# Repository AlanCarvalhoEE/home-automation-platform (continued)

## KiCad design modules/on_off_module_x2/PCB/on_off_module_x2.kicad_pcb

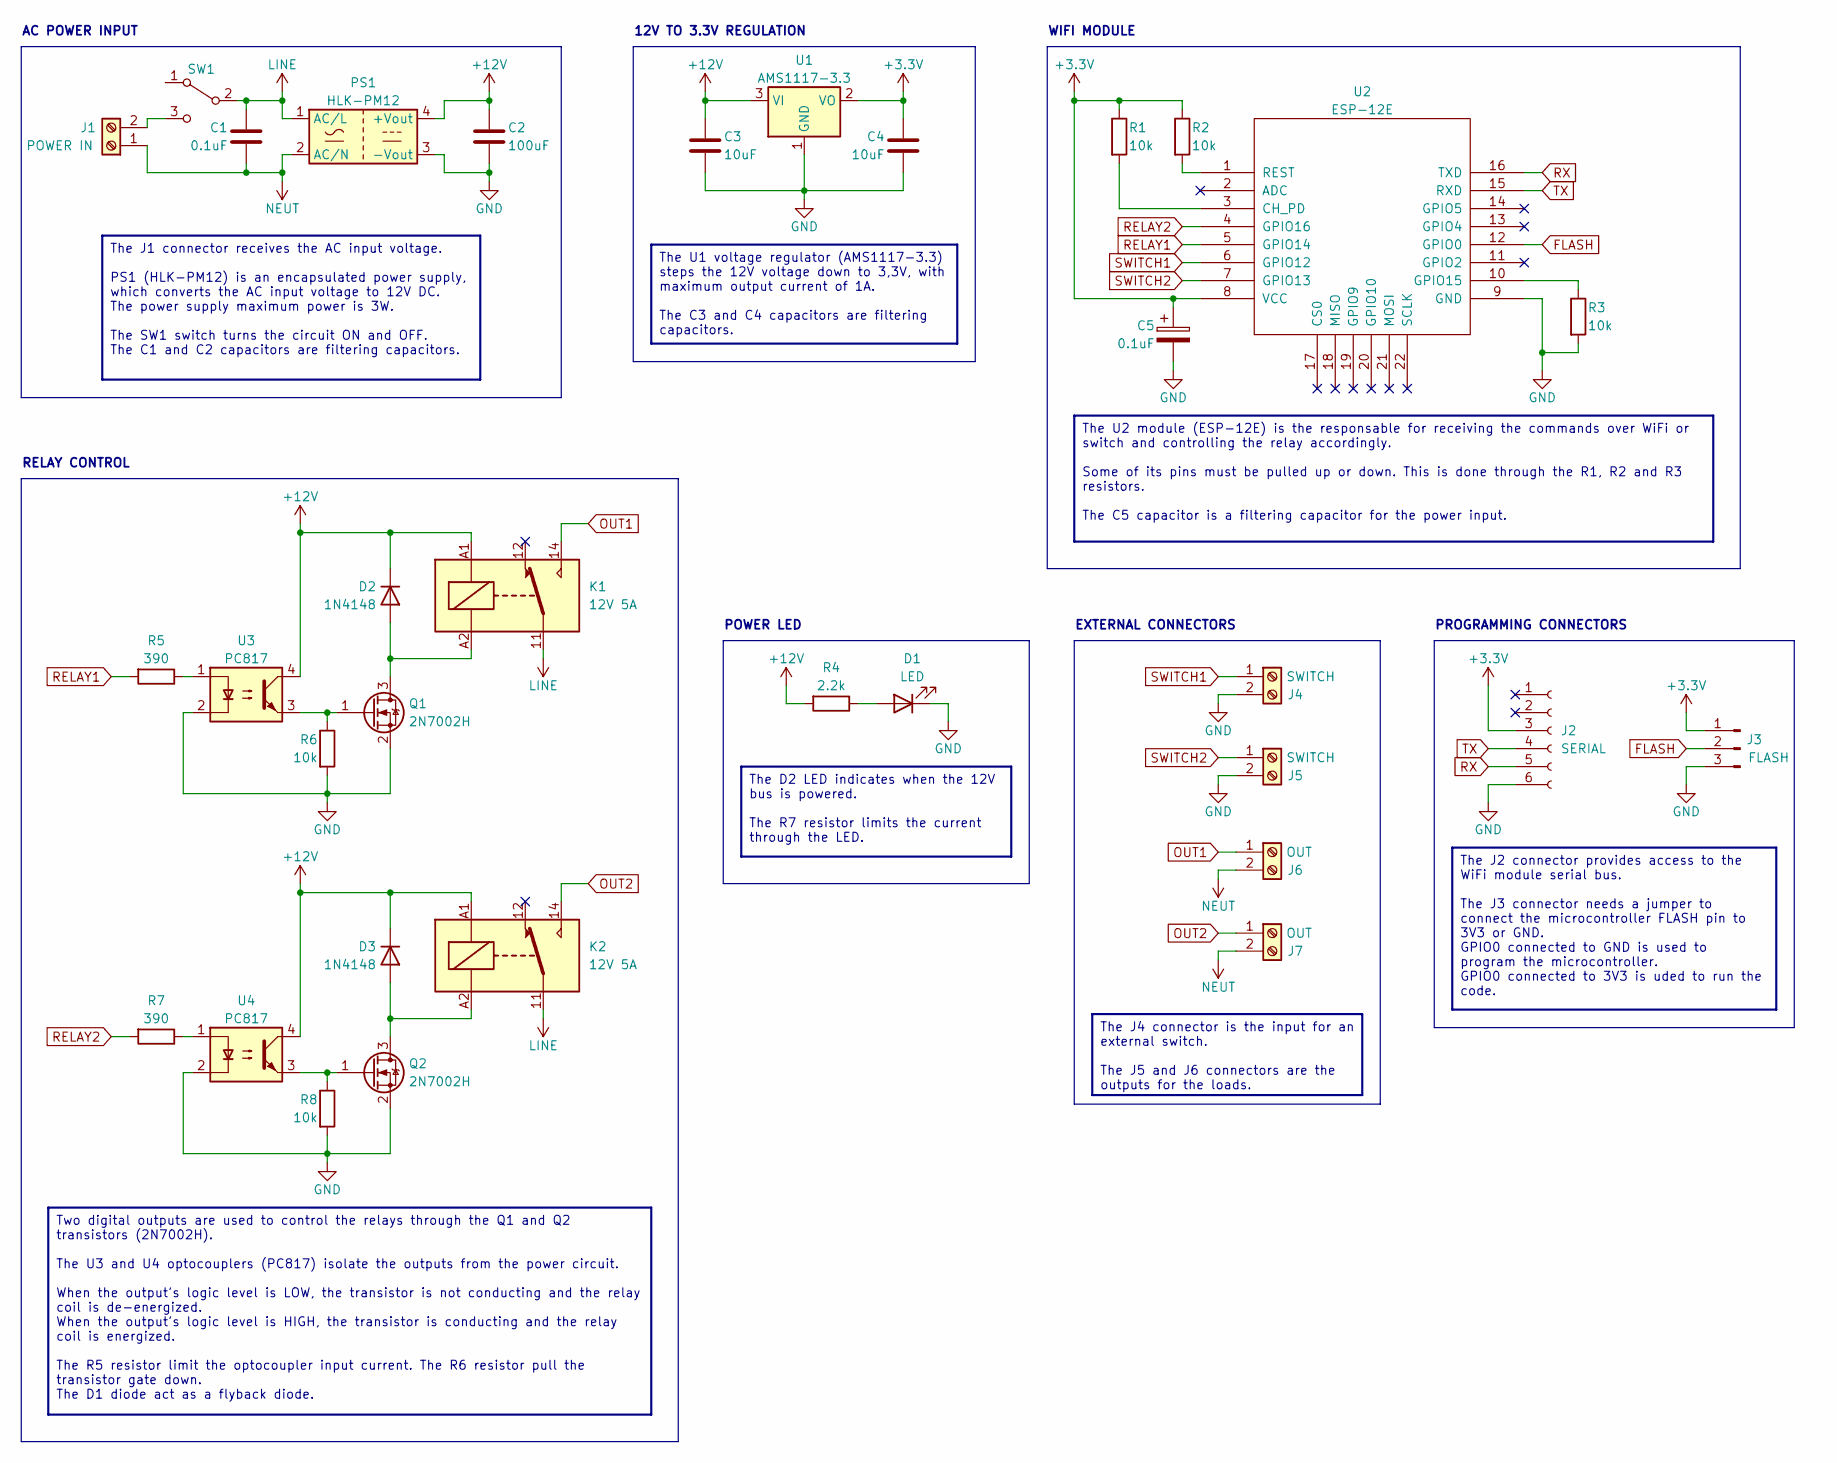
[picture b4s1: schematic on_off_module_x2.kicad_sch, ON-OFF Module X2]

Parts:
C1: 0.1uF; C_Rect_L18.0mm_W6.0mm_P15.00mm_FKS3_FKP3; Voltage 275V
C2: 100uF; CP_Elec_6.3x7.7; Voltage 16V
C3: 10uF; CP_EIA-3216-18_Kemet-A; Voltage 16V
C4: 10uF; CP_EIA-3216-18_Kemet-A; Voltage 6.3V
C5: 0.1uF; C_0603_1608Metric; Voltage 6.3V
D1: LED; LED_0603_1608Metric
D2, D3: 1N4148; D_SOD-323F
J1, J4, J5, J6, J7: Screw_Terminal_01x02; TerminalBlock_Phoenix_MKDS-1,5-2-5.08_1x02_P5.08mm_Horizont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
J2: Conn_01x06_Socket; PinHeader_1x06_P2.54mm_Vertical
J3: Conn_01x03_Socket; PinSocket_1x03_P2.54mm_Vertical
K1, K2: 12V 5A; Relay_SPDT_Finder_36.11
PS1: HLK-PM12; Converter_ACDC_HiLink_HLK-PMxx
Q1, Q2: 2N7002H; SOT-23
R1, R2, R3, R6, R8: 10k; R_0603_1608Metric; Tolerance 5%
R4: 2.2k; R_0603_1608Metric; Tolerance 5%
R5, R7: 390; R_0603_1608Metric; Tolerance 5%
SW1: SW_SPDT; Toggle_Switch_SelfLocking_7x7
U1: AMS1117-3.3; SOT-223-3_TabPin2
U2: ESP-12E; ESP-12E_SMD
U3, U4: PC817; SMDIP-4_W7.62mm

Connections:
+3.3V: C4.1, C5.1, J2.3, J3.1, R1.1, R2.1, U1.2 (VO), U2.8 (VCC)
+12V: C2.1, C3.1, D2.1 (K), D3.1 (K), K1.A1, K2.A1, PS1.4 (+Vout), R4.2, U1.3 (VI), U3.4, U4.4
FLASH: J3.2, U2.12 (GPIO0)
GND: C2.2, C3.2, C4.2, C5.2, D1.1 (K), J2.6, J3.3, J4.2, J5.2, PS1.3 (-Vout), Q1.2 (S), Q2.2 (S), R3.2, R6.2, R8.2, U1.1 (GND), U2.9 (GND), U3.2, U4.2
LINE: C1.1, K1.11, K2.11, PS1.1 (AC/L), SW1.2 (B)
NEUT: C1.2, J1.1, J6.2, J7.2, PS1.2 (AC/N)
unnamed: D1.2 (A), R4.1
unnamed: D2.2 (A), K1.A2, Q1.3 (D)
unnamed: D3.2 (A), K2.A2, Q2.3 (D)
unnamed: J1.2, SW1.3 (C)
unnamed: Q1.1 (G), R6.1, U3.3
unnamed: Q2.1 (G), R8.1, U4.3
unnamed: R5.1, U3.1
unnamed: R7.1, U4.1
unnamed: R1.2, U2.3 (CH_PD)
unnamed: R3.1, U2.10 (GPIO15)
unnamed: R2.2, U2.1 (REST)
OUT1: J6.1, K1.14
OUT2: J7.1, K2.14
RELAY1: R5.2, U2.5 (GPIO14)
RELAY2: R7.2, U2.4 (GPIO16)
RX: J2.5, U2.16 (TXD)
SWITCH1: J4.1, U2.6 (GPIO12)
SWITCH2: J5.1, U2.7 (GPIO13)
TX: J2.4, U2.15 (RXD)

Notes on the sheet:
The J1 connector receives the AC input voltage. PS1 (HLK-PM12) is an encapsulated power supply, which converts the AC input voltage to 12V DC. The power supply maximum power is 3W. The SW1 switch turns the circuit ON and OFF. The C1 and C2 capacitors are filtering capacitors.
Two digital outputs are used to control the relays through the Q1 and Q2 transistors (2N7002H). The U3 and U4 optocouplers (PC817) isolate the outputs from the power circuit. When the output's logic level is LOW, the transistor is not conducting and the relay coil is de-energized. When the output's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
The J2 connector provides access to the WiFi module serial bus. The J3 connector needs a jumper to connect the microcontroller FLASH pin to 3V3 or GND. GPIO0 connected to GND is used to program the microcontroller. GPIO0 connected to 3V3 is uded to run the code.
The D2 LED indicates when the 12V bus is powered. The R7 resistor limits the current through the LED.
The U2 module (ESP-12E) is the responsable for receiving the commands over WiFi or switch and controlling the relay accordingly. Some of its pins must be pulled up or down. This is done through the R1, R2 and R3 resistors. The C5 capacitor is a filtering capacitor for the power input.
The U1 voltage regulator (AMS1117-3.3) steps the 12V voltage down to 3,3V, with maximum output current of 1A. The C3 and C4 capacitors are filtering capacitors.
The J4 connector is the input for an external switch. The J5 and J6 connectors are the outputs for the loads.
PROGRAMMING CONNECTORS
RELAY CONTROL
POWER LED
AC POWER INPUT
EXTERNAL CONNECTORS
WIFI MODULE
12V TO 3.3V REGULATION

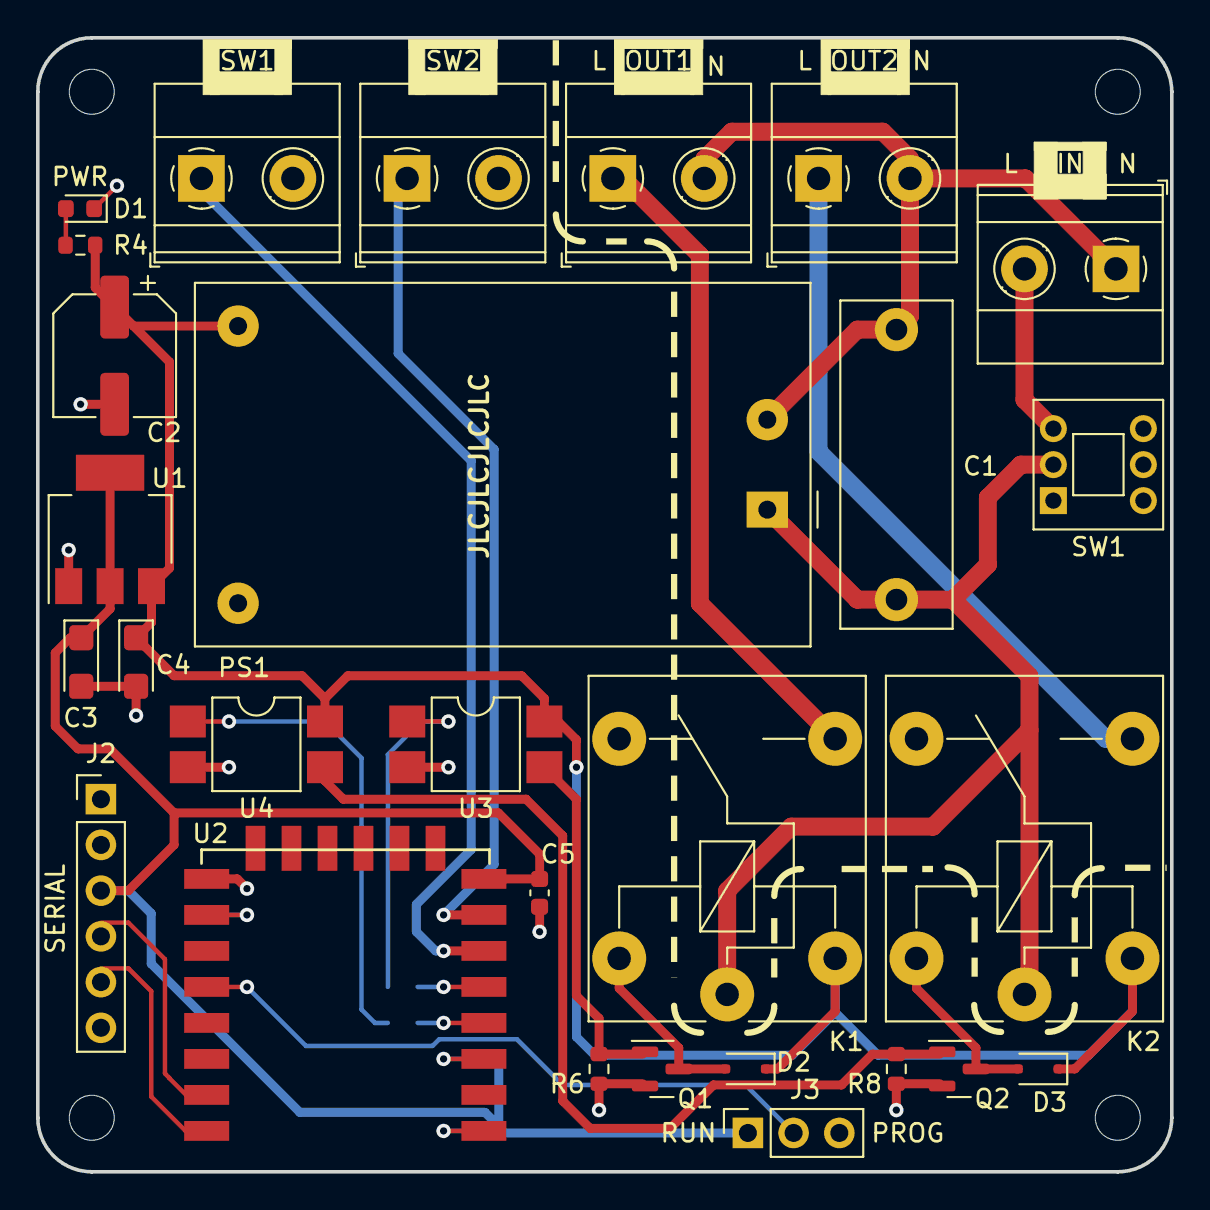
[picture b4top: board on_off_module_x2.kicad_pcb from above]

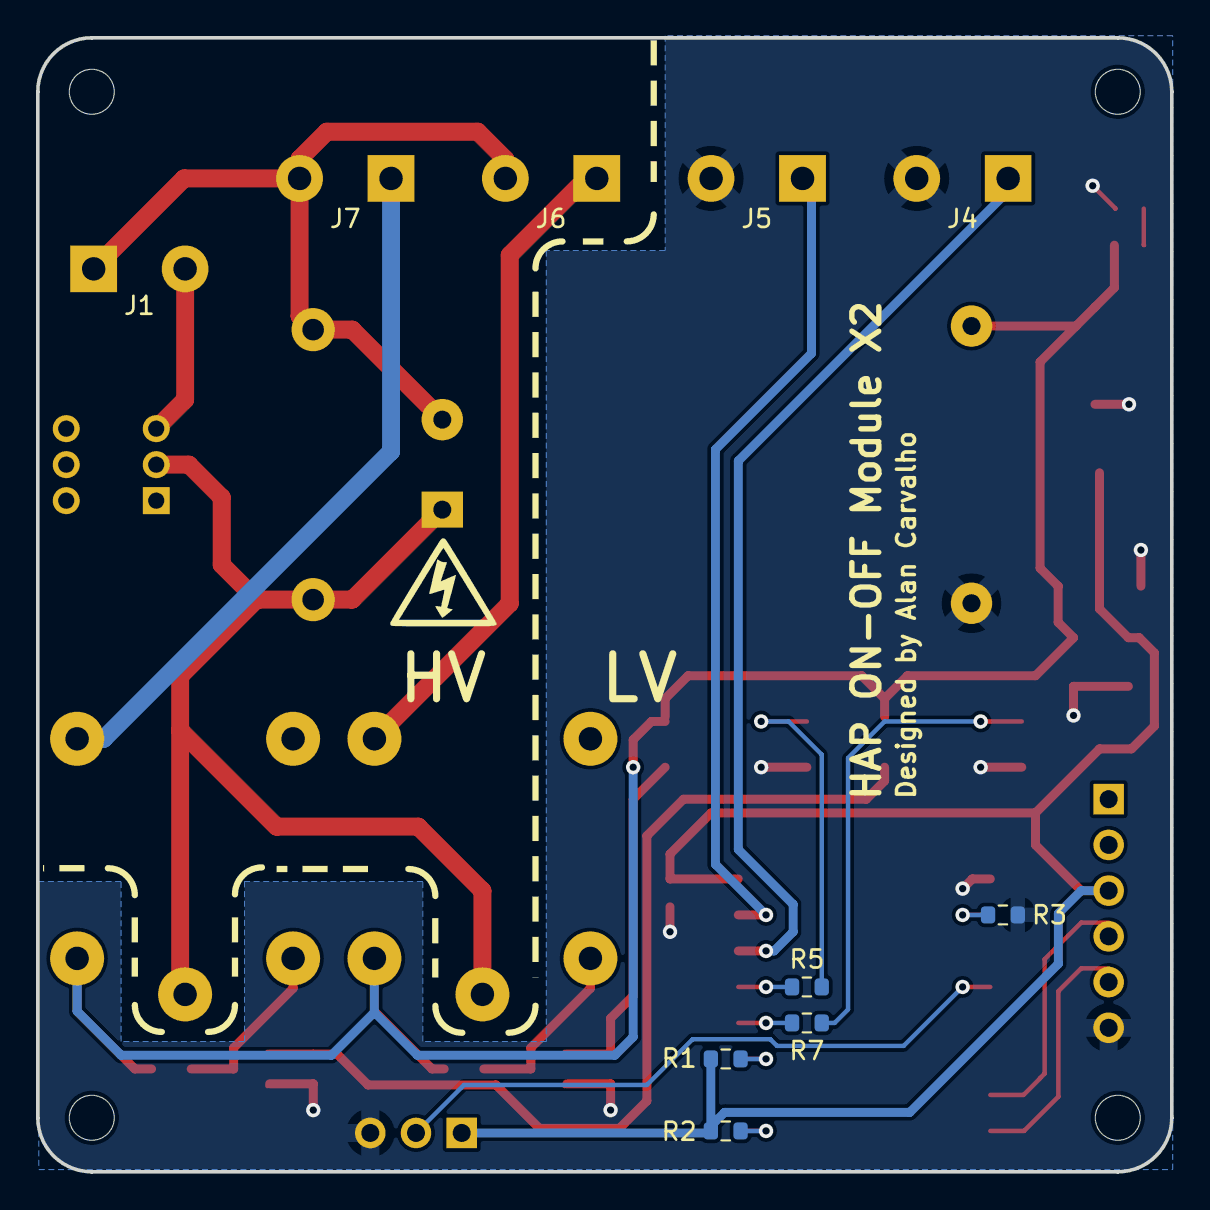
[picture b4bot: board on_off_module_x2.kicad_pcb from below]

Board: 2 copper layers, 63.0 x 63.0 mm, 33 parts (5 on the bottom side), 25 nets.

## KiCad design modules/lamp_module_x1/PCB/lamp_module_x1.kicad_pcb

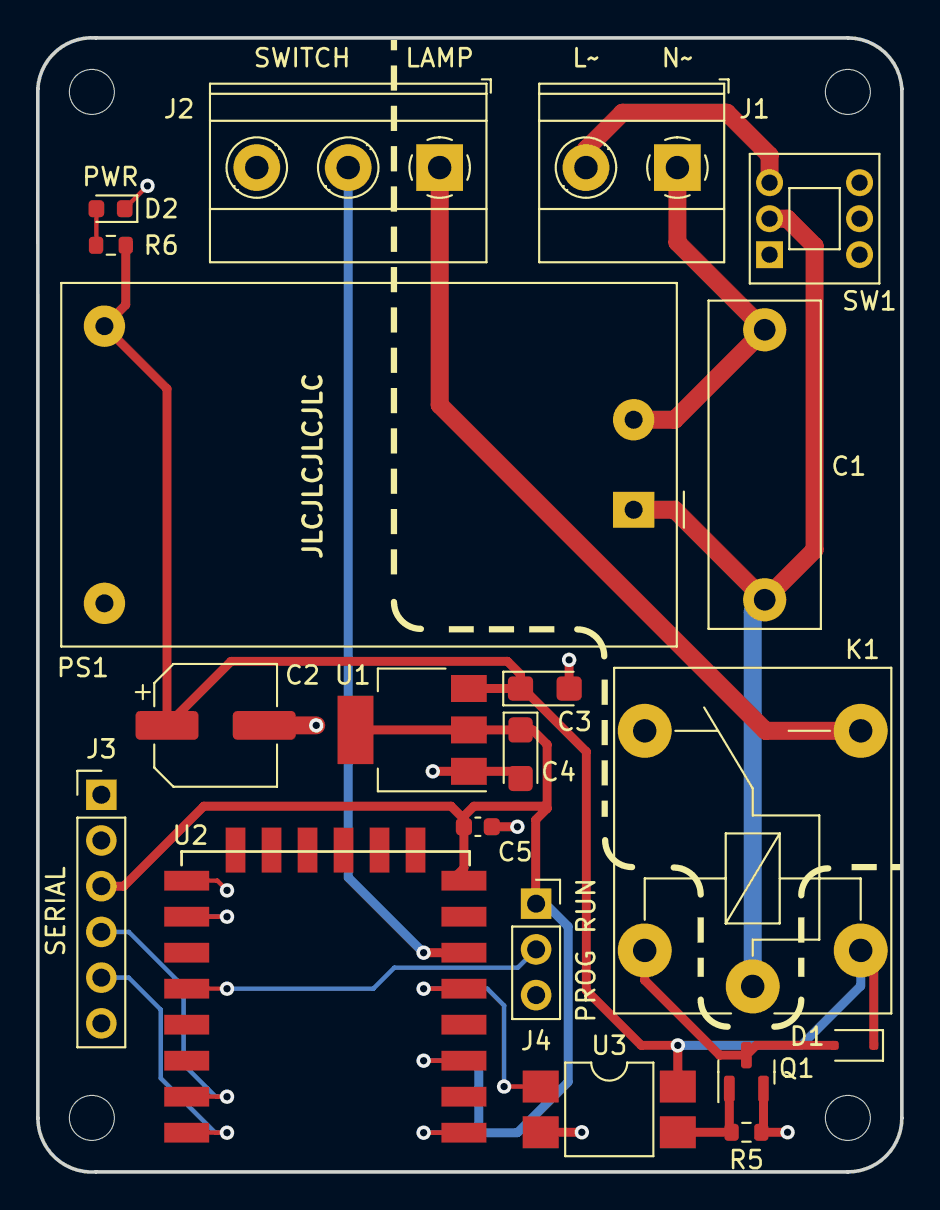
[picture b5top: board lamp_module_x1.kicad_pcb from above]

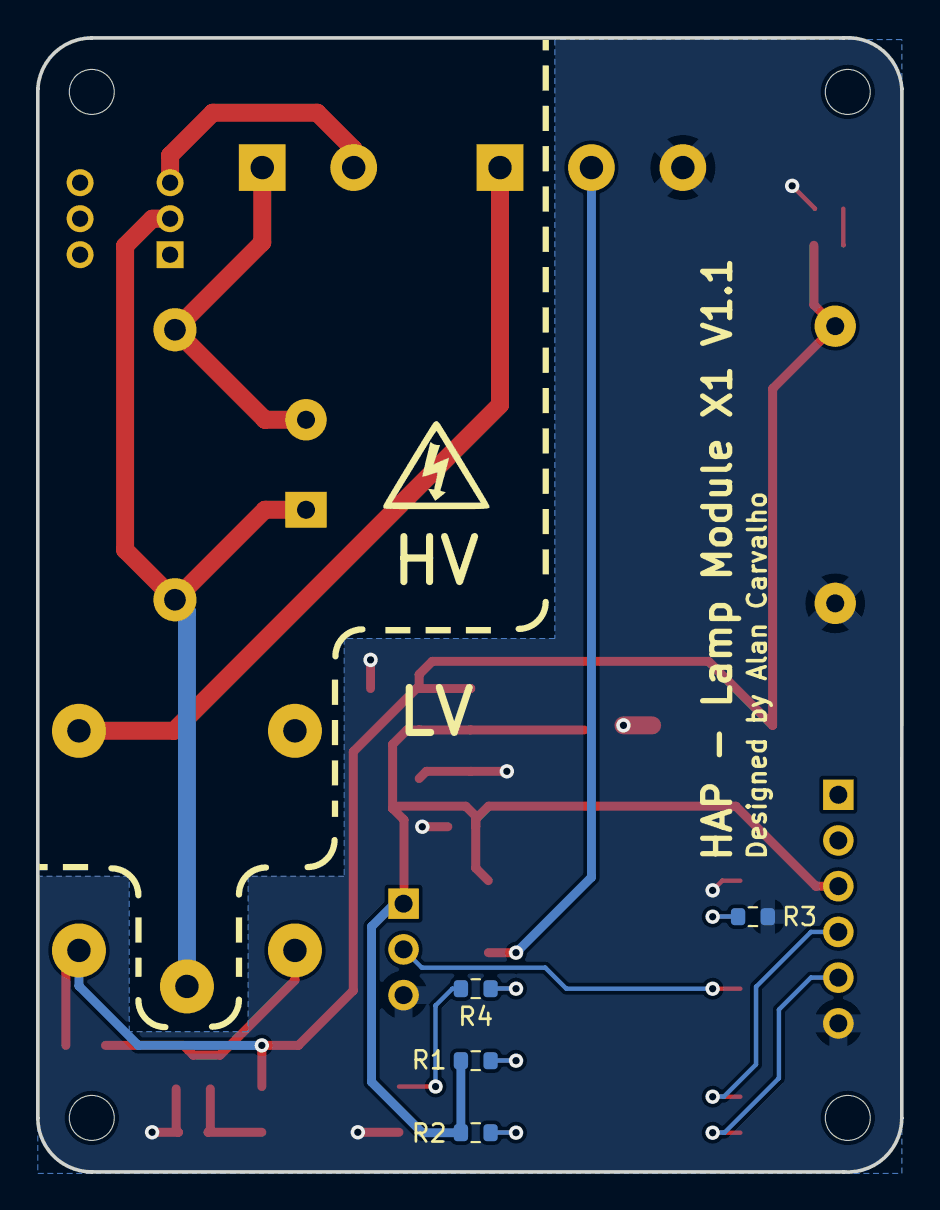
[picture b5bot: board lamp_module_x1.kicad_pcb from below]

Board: 2 copper layers, 48.0 x 63.0 mm, 24 parts (4 on the bottom side), 19 nets.

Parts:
C1: 0.1uF; C_Rect_L18.0mm_W6.0mm_P15.00mm_FKS3_FKP3
C2: 100uF; CP_Elec_6.3x7.7
C3, C4: 10uF; CP_EIA-3216-18_Kemet-A
C5: 0.1uF; C_0603_1608Metric
D1: 1N4148; D_SOD-323F
D2: LED; LED_0603_1608Metric
J1: Screw_Terminal_01x02; TerminalBlock_Phoenix_MKDS-1,5-2-5.08_1x02_P5.08mm_Horizont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
J2: Screw_Terminal_01x03; TerminalBlock_Phoenix_MKDS-1,5-3-5.08_1x03_P5.08mm_Horizont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
J3: Conn_01x06_Socket; PinHeader_1x06_P2.54mm_Vertical
J4: Conn_01x03_Socket; PinSocket_1x03_P2.54mm_Vertical
K1: 12V 5A; Relay_SPDT_Finder_36.11
PS1: HLK-PM12; Converter_ACDC_HiLink_HLK-PMxx
Q1: 2N7002H; SOT-23
R1, R2, R3, R5: 10k; R_0603_1608Metric
R4: 390; R_0603_1608Metric
R6: 2.2k; R_0603_1608Metric
SW1: SW_SPDT; Toggle_Switch_SelfLocking_7x7
U1: AMS1117-3.3; SOT-223-3_TabPin2
U2: ESP-12E; ESP-12E_SMD
U3: PC817; SMDIP-4_W7.62mm

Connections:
+3.3V: C4.1, C5.1, J3.3, J4.1, R1.1, R2.1, U1.2 (VO), U2.8 (VCC)
+12V: C2.1, C3.1, D1.1 (K), K1.A1, PS1.4 (+Vout), R6.2, U1.3 (VI), U3.4
FLASH: J4.2, U2.12 (GPIO0)
GND: C2.2, C3.2, C4.2, C5.2, D2.1 (K), J2.3, J3.6, J4.3, PS1.3 (-Vout), Q1.2 (S), R3.2, R5.2, U1.1 (GND), U2.9 (GND), U3.2
LAMP: J2.1, K1.14
LINE: C1.1, K1.11, PS1.1 (AC/L), SW1.2 (B)
NEUT: C1.2, J1.1, PS1.2 (AC/N)
unnamed: D1.2 (A), K1.A2, Q1.3 (D)
unnamed: D2.2 (A), R6.1
unnamed: J1.2, SW1.3 (C)
unnamed: Q1.1 (G), R5.1, U3.3
unnamed: R4.1, U3.1
unnamed: R1.2, U2.3 (CH_PD)
unnamed: R3.1, U2.10 (GPIO15)
unnamed: R2.2, U2.1 (REST)
RELAY: R4.2, U2.5 (GPIO14)
RX: J3.5, U2.16 (TXD)
SWITCH: J2.2, U2.6 (GPIO12)
TX: J3.4, U2.15 (RXD)

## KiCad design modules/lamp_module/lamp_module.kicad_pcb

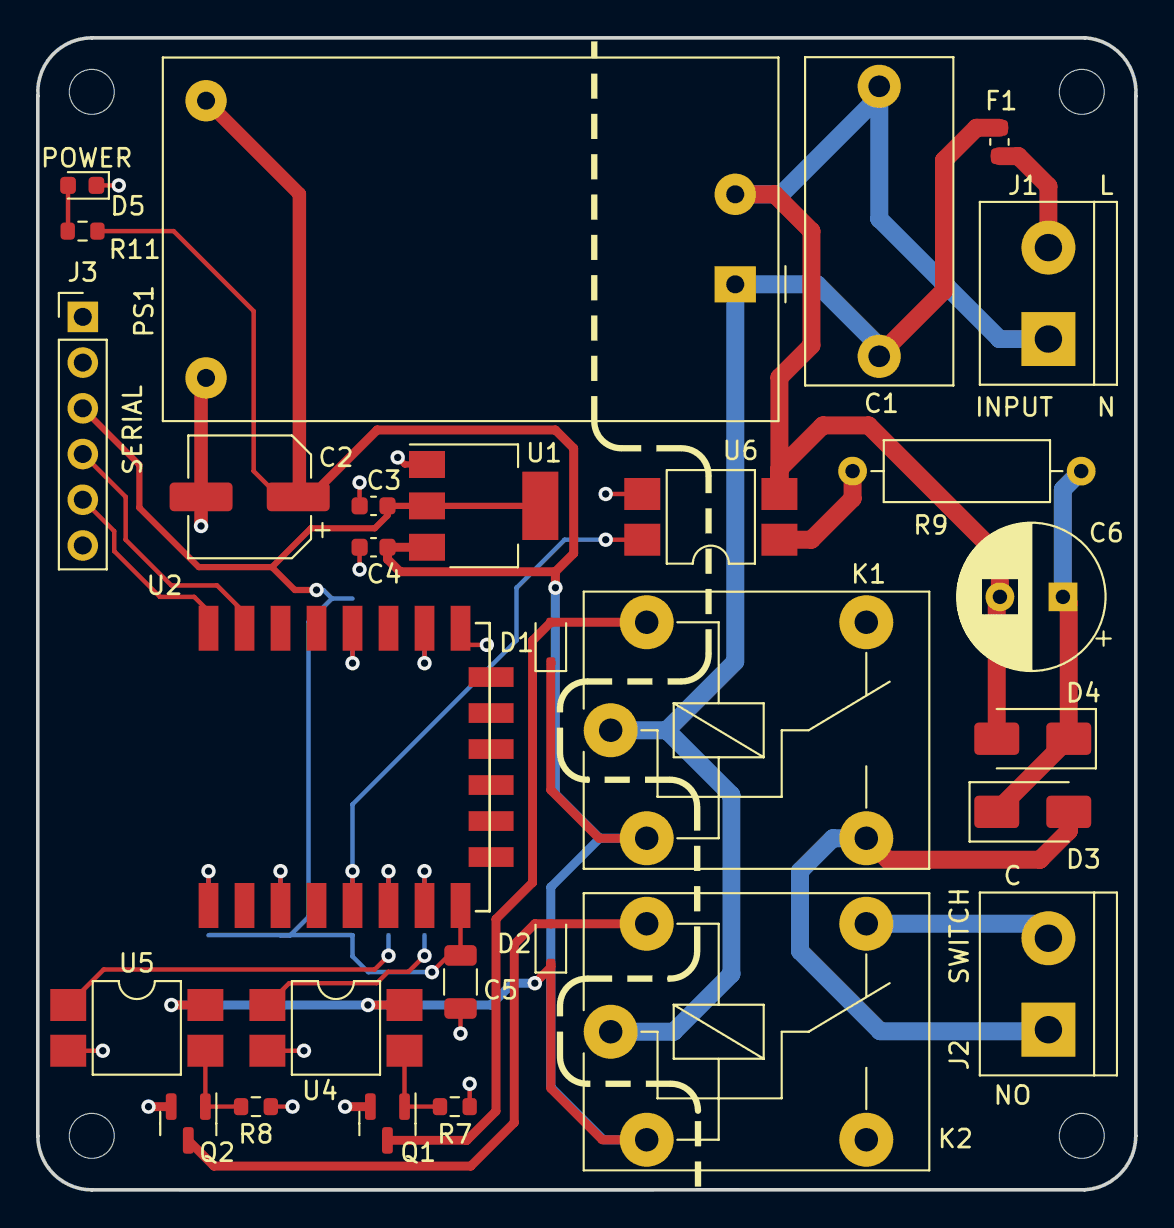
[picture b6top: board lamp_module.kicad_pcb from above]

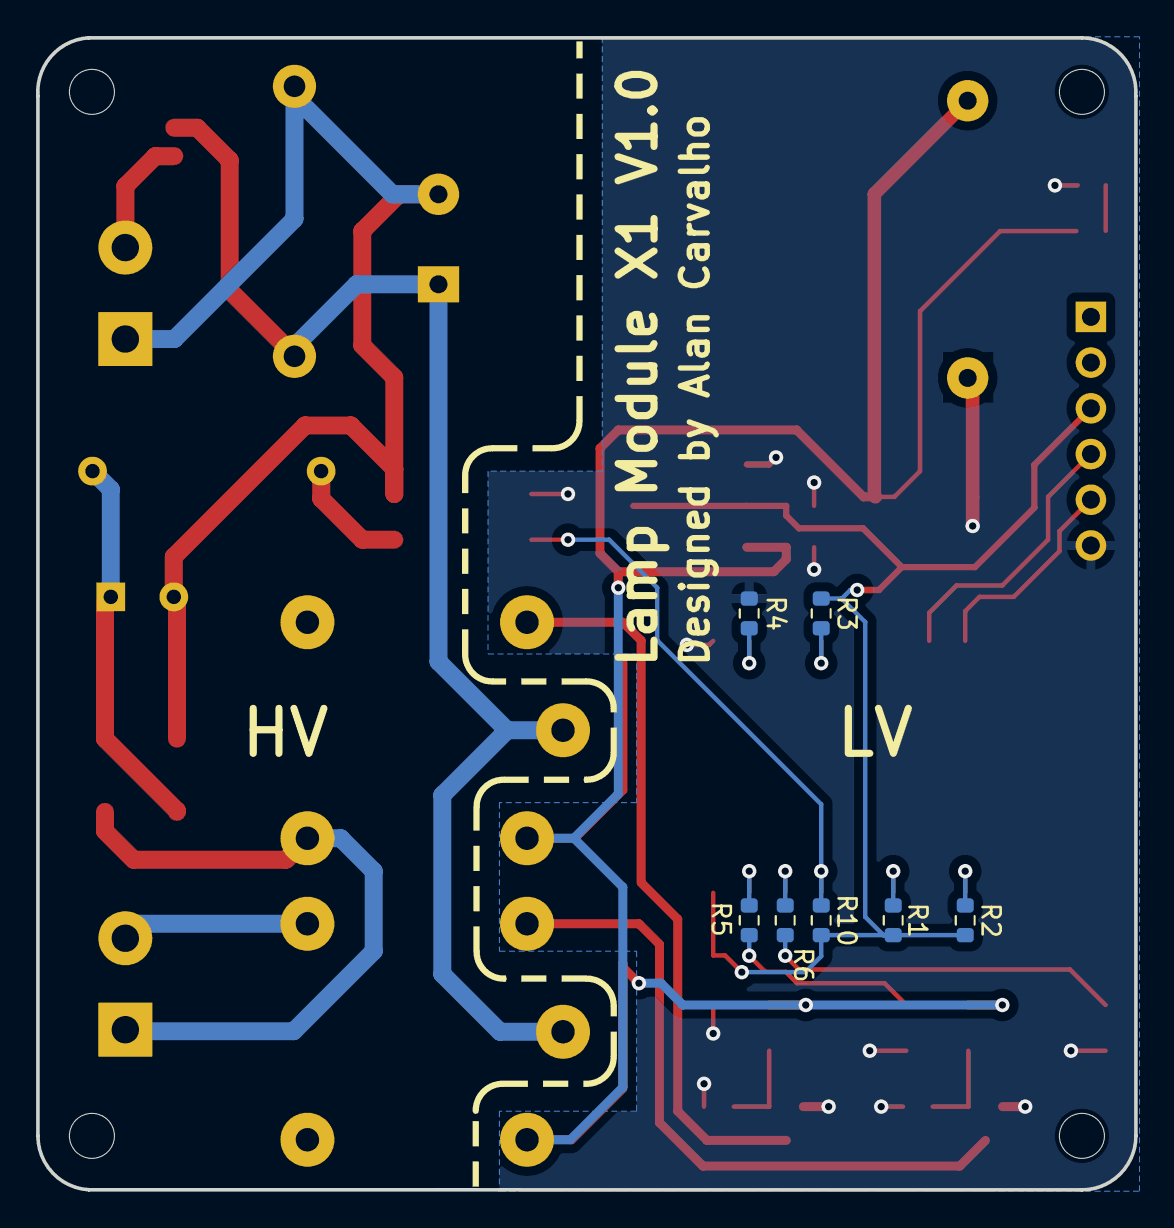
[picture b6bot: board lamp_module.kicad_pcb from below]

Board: 2 copper layers, 61.0 x 64.0 mm, 36 parts (7 on the bottom side), 26 nets.

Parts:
C1: 0.1uF; C_Rect_L18.0mm_W8.0mm_P15.00mm_FKS3_FKP3
C2: 100uF; CP_Elec_6.3x7.7
C3: 1uF; C_0603_1608Metric
C4: 22uF; C_0603_1608Metric
C5: 0.1uF; C_1206_3216Metric
C6: 1uF; CP_Radial_D8.0mm_P3.50mm
D1, D2: 1N4148; D_SOD-323F
D3, D4: 1N4007; D_SMA
D5: LED; LED_0603_1608Metric
F1: 0.5A; Fuse_0603_1608Metric
J1, J2: Screw_Terminal_01x02; TerminalBlock_bornier-2_P5.08mm
J3: Conn_01x06_Socket; PinHeader_1x06_P2.54mm_Vertical
K1, K2: 12V 5A; Relay_SPDT_Finder_36.11
PS1: HLK-PM12; Converter_ACDC_HiLink_HLK-PMxx
Q1, Q2: 2N7002H; SOT-23
R1, R2, R3, R4, R7, R8, R10: 10k; R_0603_1608Metric
R5, R6: 390; R_0603_1608Metric
R9: 56k; R_Axial_DIN0309_L9.0mm_D3.2mm_P12.70mm_Horizontal
R11: 2.2k; R_0603_1608Metric
U1: AMS1117-3.3; SOT-223-3_TabPin2
U2: ESP-12E; ESP-12E_SMD
U4, U5, U6: PC817; SMDIP-4_W7.62mm

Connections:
+3.3V: C4.1, C5.1, J3.3, R1.1, R2.1, R3.1, R10.1, U1.2 (VO), U2.8 (VCC)
+12V: C2.1, C3.1, D1.1 (K), D2.1 (K), K1.A1, K2.A1, PS1.4 (+Vout), R11.2, U1.3 (VI), U4.4, U5.4
FEEDBACK: R10.2, U2.5 (GPIO14), U6.4
GND: C2.2, C3.2, C4.2, C5.2, D5.1 (K), J3.6, PS1.3 (-Vout), Q1.2 (S), Q2.2 (S), R4.2, R7.2, R8.2, U1.1 (GND), U2.9 (GND), U4.2, U5.2, U6.3
LINE: C1.1, F1.2, K1.11, K2.11, PS1.1 (AC/L)
NEUT: C1.2, C6.2, D4.2 (A), J1.1, PS1.2 (AC/N), U6.2
unnamed: D1.2 (A), K1.A2, Q1.3 (D)
unnamed: D2.2 (A), K2.A2, Q2.3 (D)
unnamed: C6.1, D3.1 (K), D4.1 (K), R9.2
unnamed: D5.2 (A), R11.1
unnamed: F1.1, J1.2
unnamed: J2.2, K2.12
unnamed: Q1.1 (G), R7.1, U4.3
unnamed: Q2.1 (G), R8.1, U5.3
unnamed: R5.1, U4.1
unnamed: R6.1, U5.1
unnamed: R9.1, U6.1
unnamed: R1.2, U2.3 (CH_PD)
unnamed: R3.2, U2.12 (GPIO0)
unnamed: R4.1, U2.10 (GPIO15)
unnamed: R2.2, U2.1 (REST)
RELAY_P: R5.2, U2.7 (GPIO13)
RELAY_S: R6.2, U2.6 (GPIO12)
RX: J3.5, U2.16 (TXD)
SWITCH_NO: D3.2 (A), J2.1, K1.14
TX: J3.4, U2.15 (RXD)

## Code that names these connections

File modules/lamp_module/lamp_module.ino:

#include <ESP8266WiFi.h>
#include <Arduino.h>


#define ID 1

#define RELAY_S_PIN 12             // Series relay pin
#define RELAY_P_PIN 13             // Parallel relay pin
#define FEEDBACK_PIN 14            // Voltage feedback pin


// Network parameters
const char* ssid = "Mhnet - Luana_2.4G";
const char* password = "dracarys";
IPAddress serverIP (192,168,88,11); 
IPAddress moduleIP (192,168,88,20); 
IPAddress gateway (192,168,88,1); 
IPAddress subnet (255,255,255,0);
const uint16_t serverPort = 5560;

WiFiClient tcpClient;   // TCP client instance


void setup() 
{
  pinMode(RELAY_S_PIN, OUTPUT);
  pinMode(RELAY_P_PIN, OUTPUT);
  pinMode(FEEDBACK_PIN, INPUT);

  Serial.begin(115200);                       // Start the serial port
  while (!Serial) delay(50);                  // Wait until the serial port is open

  WiFi.mode(WIFI_STA);                        // Configure the WiFi mode to STATION
  WiFi.begin(ssid, password);                // Configure the WiFi connection credentials
  WiFi.config(moduleIP, gateway, subnet);
  tcpClient.setTimeout(50);

  Serial.print("Waiting for WiFi... ");

  while (WiFi.status() != WL_CONNECTED)     // Wait until the WiFi interface is ready
  {
    Serial.print(".");
    delay(500);
  }

  Serial.println("");
  Serial.println("WiFi connected");
  Serial.print("IP address: ");
  Serial.println(WiFi.localIP());

  while (!tcpClient.connect(serverIP, serverPort)) {
    Serial.println("connection failed");
    delay(5000);
  }

  delay(500);
}


void loop() 
{   
  if (tcpClient.available())
  {
    String command = tcpClient.readString();

    if (command.indexOf("ON") > -1) digitalWrite(RELAY_S_PIN, HIGH);
    else if (command.indexOf("OFF") > -1) digitalWrite(RELAY_S_PIN, LOW);
  }
}

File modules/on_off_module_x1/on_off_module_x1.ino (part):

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#include "credentials.h"

// Device Parameters
#define TOPIC "lamp"
#define SET_STATE_TOPIC "set_state"
#define GET_STATE_TOPIC "get_state"
#define ENABLE_LDR_TOPIC "enable_ldr"
#define ADJUST_LDR_TOPIC "adjust_ldr"

// Pins
#define SWITCH_PIN 12
#define RELAY_PIN 14
#define LDR_PIN A0

// Client instances
WiFiClient tcpClient;
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bool ldrEnabled = false;                      // Defines whether the LDR is enabled or not
bool wifiConnected = false;                   // WiFi connection status (Connected = true, Disconnected = false)
bool brokerConnected = false;                 // Broker connection status (Connected = true, Disconnected = false)
unsigned int ldrReading = 0;                  // LDR reading value (0 to 1023)
unsigned int ldrThreshold = 600;              // Threshold to turn the output ON or OFF based on LDR input 
const unsigned int ldrHisteresis = 50;        // Histeresis to avoid output flickering
unsigned long lastWifiCheck = 0;              // Last time the WiFi connection was checked (ms)
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const long brokerCheckInterval = 5000;        // Interval to check the broker connection (ms)
unsigned long lastReportPrint = 0;            // Last time the report was printed (ms)
const long reportPrintInterval = 500;         // Interval to print the report (ms)
unsigned long lastSwitchChange = 0;           // Last time the switch state has changed (ms)
const long debounceInterval = 500;            // Interval to debounce the switch state changing (ms)
unsigned long lastLdrCheck = 0;               // Last time the LDR input was checked (ms)
const long ldrCheckInterval = 10000;          // Interval to check the LDR input (ms)
String setStateTopic;                         // Topic for setting the module state
String getStateTopic;                         // Topic for retrieving the module state
String enableLdrTopic;                        // Topic for enabling and disabling the LDR
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  delay(5000);

  // Configure the GPIO
  pinMode(SWITCH_PIN,INPUT_PULLUP);
  pinMode(RELAY_PIN, OUTPUT);
  pinMode(LDR_PIN,INPUT);

  // Starts with the load turned OFF
  digitalWrite(RELAY_PIN, loadOn);

  // Start the EEPROM with 4 bytes
  EEPROM.begin(4);
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
  if (strcmp(topic, setStateTopic.c_str()) == 0) {
    if (message == "ON") {
      digitalWrite(RELAY_PIN, HIGH);
      loadOn = true;
    } 
    else if (message == "OFF") {
      digitalWrite(RELAY_PIN, LOW);
      loadOn = false;
    }
  }
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void checkSwitch() {

  // If the switch has been pressed...
  if (digitalRead(SWITCH_PIN) == LOW && ((millis() - lastSwitchChange) > debounceInterval)) {
    
    // Change the load state
    loadOn = !loadOn;
    digitalWrite(RELAY_PIN, loadOn);

    publishState();   // Publish the state to the broker

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  // Check every few seconds to avoid flickering
  if ((millis() - lastLdrCheck) > ldrCheckInterval) {
  
    ldrReading = analogRead(LDR_PIN);   // Read the LDR

    // If LDR threshold has been crossed...
    if (!loadOn && (ldrReading > (ldrThreshold + ldrHisteresis))) {
      digitalWrite(RELAY_PIN, HIGH);
      loadOn = true;
    }
    else if (loadOn && (ldrReading < (ldrThreshold - ldrHisteresis))) {
      digitalWrite(RELAY_PIN, LOW);
      loadOn = false;
    }

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    else (Serial.println("Disconnected"));

    Serial.print("Switch Status: ");
    if (digitalRead(SWITCH_PIN) == LOW) Serial.println("Pressed");
    else Serial.println("Not pressed");

    Serial.print("LDR Status: ");
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
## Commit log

2023-09-22 Minimal functional version
2023-09-22 General comments and indentation fixes
2023-09-22 Deleted old file tcp-server.py
2023-09-22 Deleted old file tcp-server.py.swp
2023-09-22 Changed folder structure
2023-09-22 Android project created
2023-09-24 Main window created
2023-09-24 Room controls container created
2023-09-24 Database manager integrated
2023-09-26 Location and device input dialogs created
2023-09-26 New location database input implemented
2023-09-28 New device database input implemented
2023-09-28 General code cleanup
2023-09-29 Database handling improved
2023-09-29 Device designator numbering fixed
2023-09-29 Rooms and devices update implemented in the configuration window
2023-09-29 Main page loading from database implemented
2023-09-30 General layout improvements
2023-09-30 Dialogs layout improved
2023-10-01 Relays control adjusted
2023-10-01 TCP client implemented
2023-10-01 Comments included
2023-10-01 README updated
2023-10-07 Air conditioner status control implemented
2023-10-07 Air conditioner basic control implemented
2023-10-07 Air conditioner module first version
2023-10-07 Old unused files deleted
2023-10-10 Removed the main database from the Android device
2023-10-10 Server database implemented
2023-10-10 Database handling bugs fixed
2023-10-12 Database update function implemented
2023-10-12 Introduction screen implemented
2023-10-13 Introduction screen improved
2023-10-16 Created a class for the commom functions
2023-10-17 Created components for some devices
2023-10-17 Converted the TCPclient class to a singleton pattern
2023-10-17 Converted the DBHandler class to a singleton pattern
2023-10-17 Togglebutton listener for ON/OFF devices implemented
2023-10-17 Air conditioner temperature control implemented
2024-01-18 Lamp module PCB schematic created
2024-01-20 Lamp module PCB V1.0 finished
2024-02-21 Lamp module 3D model finished
2024-02-21 gerber files generated
2024-05-02 PCB simplified and improved
2024-05-02 Database update bug solved
2024-05-03 Lamp module X1 firmware V1.0 finished
2024-05-06 Screen update implemented on adding room or device
2024-05-06 Lamp control function implemented
2024-05-06 Visual aspects improved.
2024-05-06 Device IP address included on database
2024-05-07 Minor changes in messages syntax
2024-05-07 Gerber and image files updated
2024-05-08 Switch feedback implemented
2024-05-08 General code refactoring
2024-05-09 Lamp manual action feedback implemented
2024-05-09 Manual action feedback implemented
2024-05-09 Lamp module X1 PCB finished
2024-05-09 Fabrication files updated
2024-05-10 PCB fabrication files updated
2024-05-10 PCB gerber updated
2024-05-13 Database device deletion implemented
2024-05-13 Devices deletion implemented
2024-05-15 Camera streaming implemented
2024-05-28 Switch debounce implemented
2024-06-07 3D assembly updated
2024-06-08 Relay pin shanged
2024-06-08 Images included
2024-06-13 Small code optimization
2024-06-13 Lamp control module assembly improved
2024-06-13 Changed switch reading logic
2024-06-17 Lamp control assembly finished
2024-06-20 Sensor module schematic created
2024-06-22 Sensor module PCB layout started
2024-06-27 Sensor module PCB layout finished
2025-03-27 ON-OFF module hardware updated to V2
2025-03-28 Wall switch module 3D model upgraded
2025-03-28 ON-OFF module X1 3D model updated
2025-08-24 Code structure migrated to MQTT
2026-01-29 General files structure refactoring
2026-01-29 General file structure refactoring
2026-01-29 Organize Android app under mobile/
2026-01-29 Organize PCB project and firmware under hardware/and firmware/
2026-01-29 Images organized under docs/images/
2026-01-29 KiCad backup and cache files removed
2026-01-29 Python bakups and run data removed
2026-01-29 Included non-tracked files to .gitignore
2026-01-31 Architecture diagram added to docs/diagrams/.
2026-01-31 Added the system diagram source file to docs/diagrams/source.
2026-01-31 README.md updated.
2026-02-05 Server auto-start implemented on file server/services/server-auto-start.service.
2026-02-07 Device auto-discovery implemented on device's firmware.
2026-02-15 Refactored database-related methods.
2026-02-18 Implemented device auto-discovery on Android APP.
2026-02-20 Refactored Utils class methods to new classes.
2026-02-20 Implemented new device/room manipulation methods
2026-02-21 Firmware OTA implemented on firmware.
2026-03-04 Refactored rooms and devices related classes.
2026-03-05 Devices's online/offline status implemented on Android APP.
2026-03-11 OTA functionality implemented on Android APP.
2026-03-12 OTA interface improved.
2026-03-15 Language selection implemented on APP.
2026-03-19 Log screen implemented on Android APP.
2026-03-19 Organized java files in subdirectories.
2026-03-26 Refactored dbhandler.py.
2026-03-26 Database structure and methods refactored.
2026-03-26 Solved multiple Android APP warnings.
2026-03-26 Implemented LDR control.
2026-03-28 LDR configuration via MQTT implemented.
2026-04-03 Fixed low responsiveness bug.
2026-04-16 Button click flickering fixed.
2026-04-25 ZeroTier One app integration done.
2026-04-30 Room filtering improved on Android APP.
2026-04-30 ON-OFF module wiring diagram included.
2026-05-01 Server log implemented
2026-05-07 Centralized credentials and configurations
2026-05-07 Included setup files
2026-05-18 Setup files corrected.
2026-05-20 Connection attempt via local network and VPN implemented.
2026-05-20 Setup information included.
2026-05-20 Fixed some syntax errors.
2026-05-27 Camera streaming implemented.
